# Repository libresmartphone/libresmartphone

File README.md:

Libre Smartphone - Open hardware phone
======================================

This page contains the software used in the open hardware smartphone, related projects files and documentation. Mechanical ([Freecad](http://freecadweb.org/)) and PCB schematic ([Kicad](http://kicad-pcb.org/)) designs will be added here in the future. Visit [libresmartphone.com](http://libresmartphone.com/open-hardware-smartphone/) or our [YouTube channel](https://www.youtube.com/channel/UC1UttFNKDiN2uA525Pe3ijA) for more information.

## Objective

Libresmartphone is a smartphone that can be connected to a bigger screen and used as a desktop computer to edit documents, watch videos, listen to music, edit images, videos and much more.

Our goal is to have a 6" screen, HDMI output, cameras, Bluetooth, WiFi, GPS, 4G or better and GSM. It will also have two or more micro-usb ports that will allow you to connect a printer or other peripherals.

It will be [Open Software](https://en.wikipedia.org/wiki/Open-source_software) and [Open Hardware](https://en.wikipedia.org/wiki/Open-source_hardware), designed with free software (Kicad) to let other users study, change and improve both the software and the hardware.

The design will allow one to add hardware kill switches for the camera, GPS, 4G, GSM.  This offers security & privacy for those who want full control over their devices.

## Roadmap

1. Make a [Raspberry Pi](https://www.raspberrypi.org/) prototype work as desired (Estimated time: 3 months – 1 year)(Estimated cost: <500€):
   * Software to make calls, send/receive SMS (with the [Adafruit 3G Fona](https://www.adafruit.com/product/2696) or similar), import contacts (csv) and take photos in any GNU/linux or BSD OS.
   * GPS navigation with navit.
   * Easy to make case (MDF) / CAD files to 3d print the case.
   * 7" capacitive screen from the Raspberry Pi foundation.
   * Make a manual so every user with a Raspberry Pi can achieve a working prototype easily.

   *The Raspberry Pi prototype will attract a larger user base for the project (currently there are 8 million Raspberry Pi in the market and a lot of their users are DIY enthusiast). Many of them are not willing to pay for an open source smartphone but would love to make calls with the Raspberry Pi, send SMS for their projects, build an simple GPS unit for their car, etc.*

2. Make a prototype with the components more open (Estimated time: 6 months – 4 years)(Estimated cost: 500-40.000€):
   * Use a more open HW board (A64 OLinuXino or similar) instead of the Raspberry Pi.
   * Use a more open HW screen (Manga Screen or similar) or design a 6" capacitive screen if there isn't any open hardware option available at that time (initiate a crowdfunding campaign to let others interested contribute).
   * Use a more open HW modem breakout if there is one available instead of the Adafruit 3G or design a LTE (PLS8-E) or better modem breakout (try to make a crowdfunding campaign to let others interested contribute).

   *The prototype will have replaceable parts if better / smaller alternatives appear in the market.*

   *If no suitable screens or modem breakout are found, a crowdfunding campaign will be made. The reason to make it that way is because there are other people that could want these parts for a different project and help to make it possible faster. Even if there is not enough people willing to support a crowdfunding campaign, the current people interested in making libresmartphone are able to pay Elias Bakken, Nikolaus Schaller or others to make them.*

*When the prototype has the size and requirements desired, libresmartphone development will start part 3.*

3. Libresmartphone final design (Estimated time: <2 years)(Estimated cost: 50.000-200.000€).
   * Design a pcb that has the CPU, GPU, RAM, modem, WiFi, etc in the same board taking in consideration all the designs used in part 2 of the development.
   * Design a case to fit all the components inside that is easy to 3D print. If there are enough people interested an injection case could be made.

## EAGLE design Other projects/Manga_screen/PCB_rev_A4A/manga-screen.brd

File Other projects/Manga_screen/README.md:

```                                                                                                                       
    _/      _/                                                _/_/_/                                                   
   _/_/  _/_/    _/_/_/  _/_/_/      _/_/_/    _/_/_/      _/          _/_/_/  _/  _/_/    _/_/      _/_/    _/_/_/
  _/  _/  _/  _/    _/  _/    _/  _/    _/  _/    _/        _/_/    _/        _/_/      _/_/_/_/  _/_/_/_/  _/    _/   
 _/      _/  _/    _/  _/    _/  _/    _/  _/    _/            _/  _/        _/        _/        _/        _/    _/    
_/      _/    _/_/_/  _/    _/    _/_/_/    _/_/_/      _/_/_/      _/_/_/  _/          _/_/_/    _/_/_/  _/    _/     
                                     _/                                                                                
                                _/_/                                                                                                                                                                                                          
```
Manga Screen is a 4.3" LCD panel with capacitive multi touch and HDMI input. It's been developed for use with 3D-printers, but can be used for any embedded project 
where the main board has USB and HDMI output. The license is CC BY-SA. 

### What is in here? ###

* This repository contains the files needed to reproduce the PCB and continue development.
* The latest revision is A4A

### I want to build my own board. How do I do that? ###

* Download the BOM and order the parts from Digi-key
* Send the GERBER files to a PCB manufacturer
* Get a reflow oven
* Populate the board

### Who do I talk to? ###

* Repo owner is Elias Bakken (elias dot bakken at gmail dot com) 
* Get in touch if you need Manga Screen with special requirements.

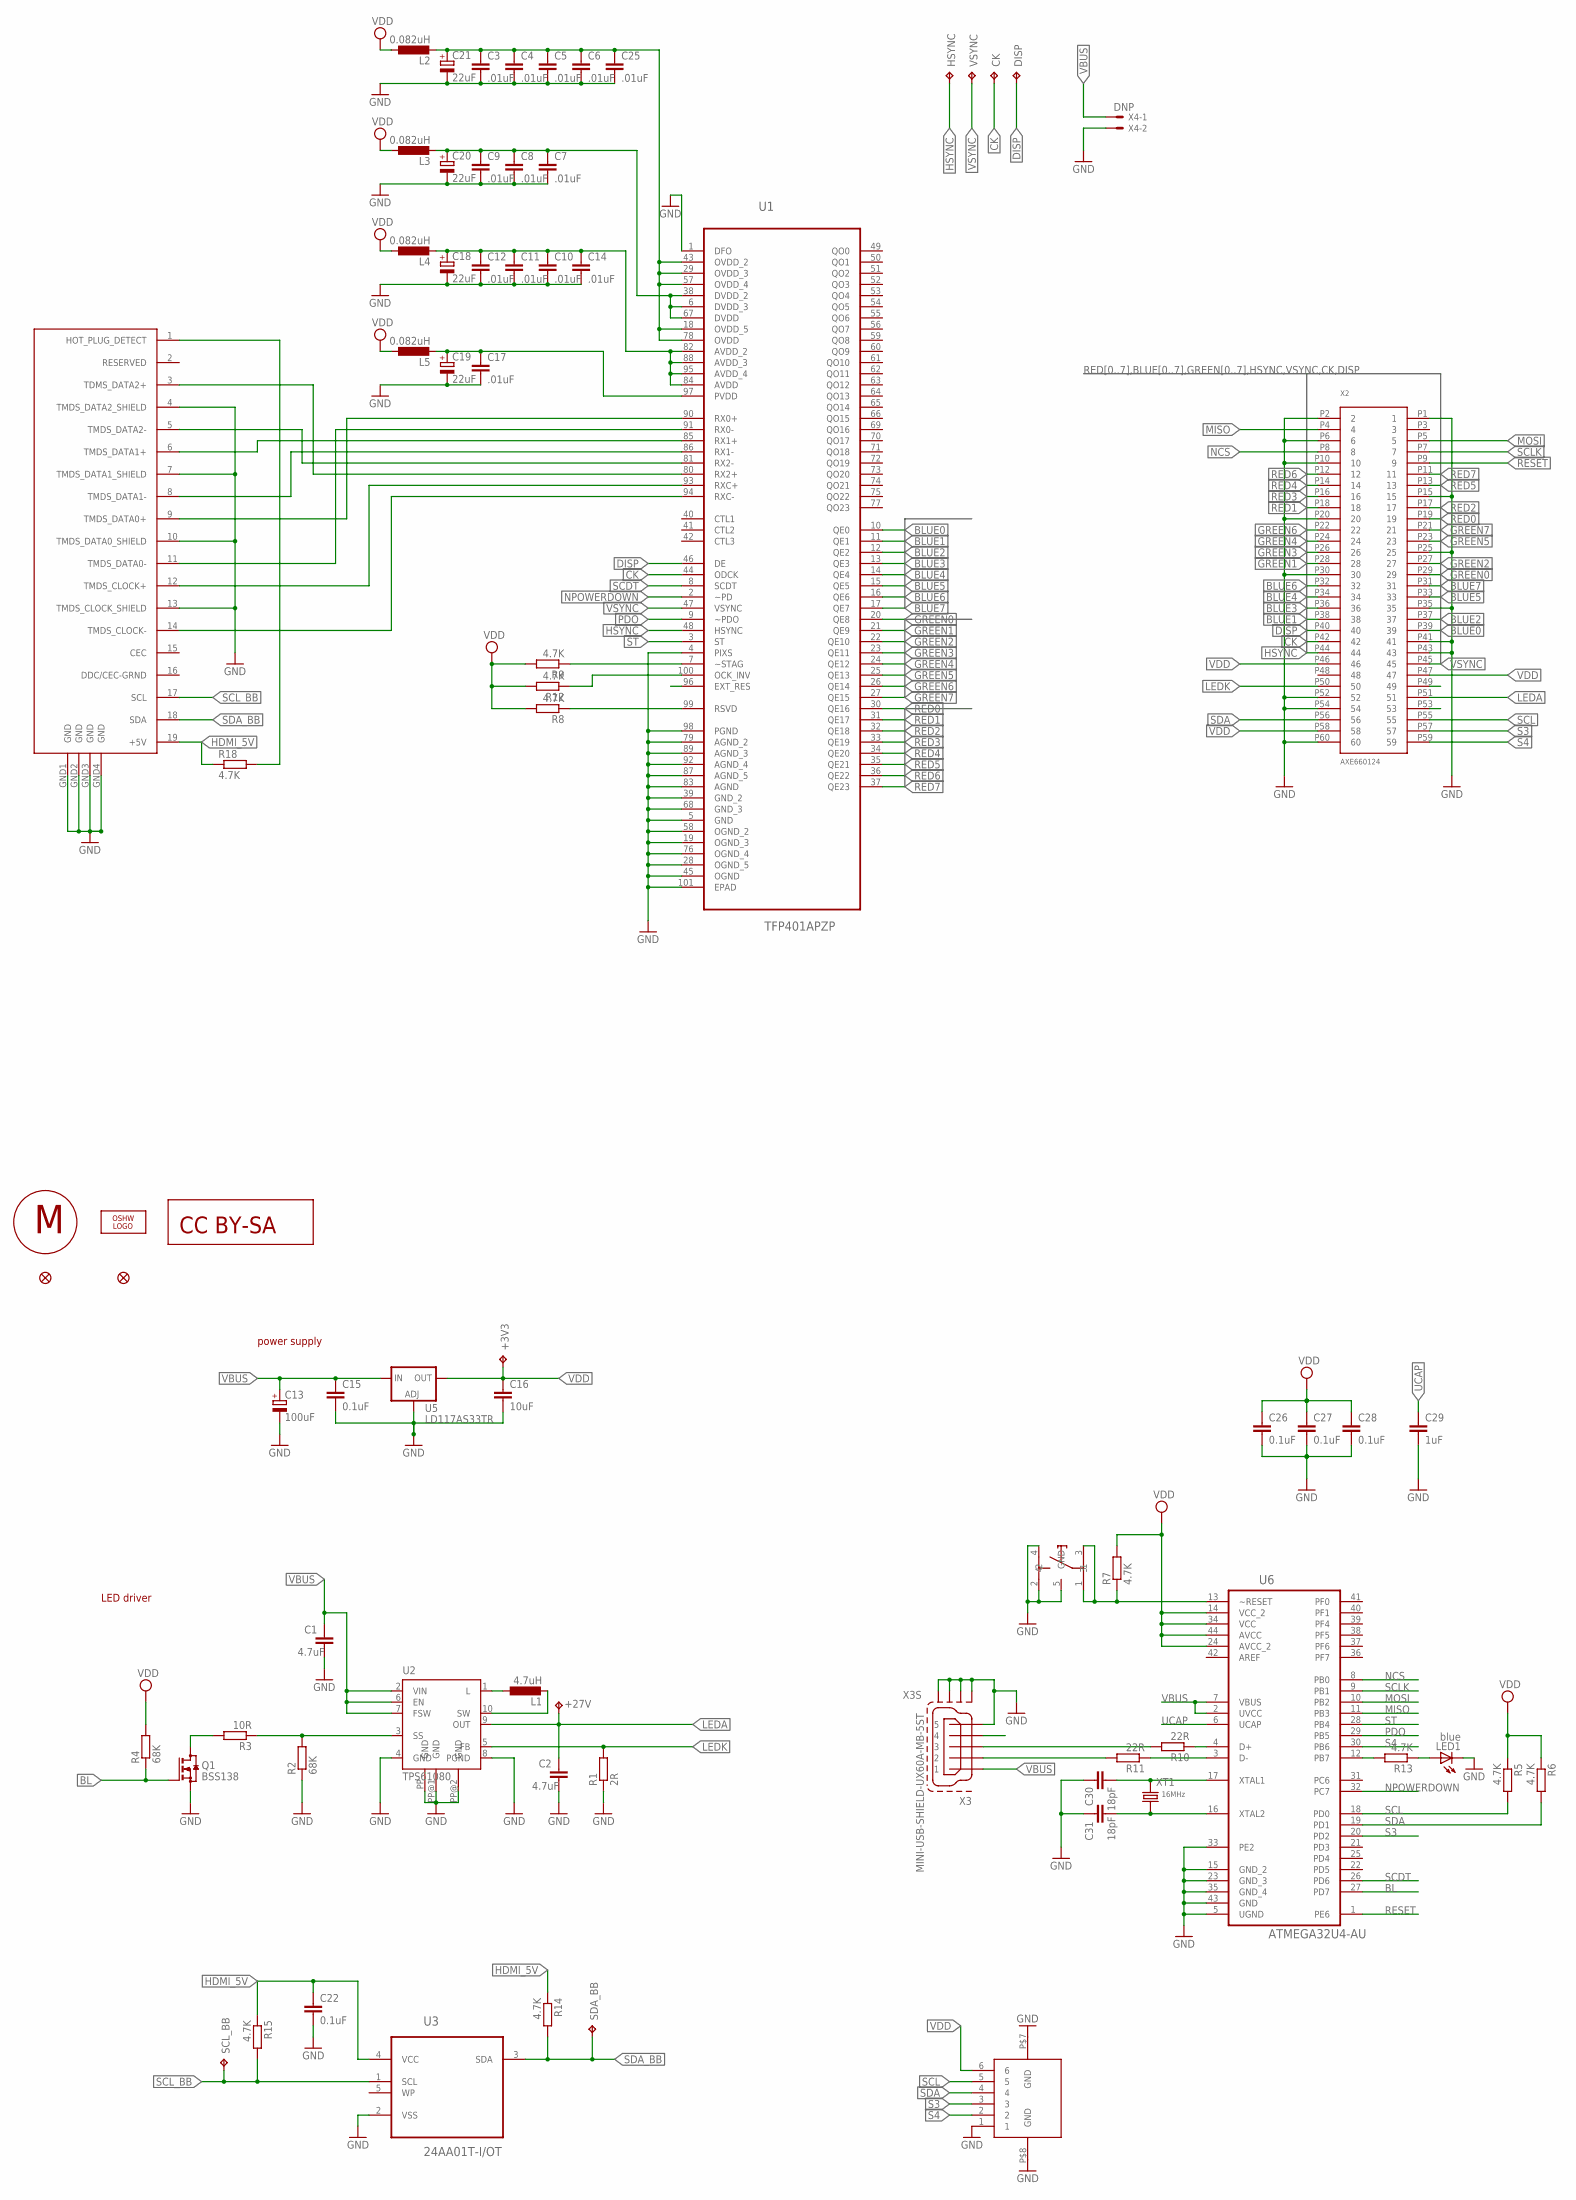
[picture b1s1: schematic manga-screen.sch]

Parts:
+3V3, +27V: TPB1,27; B1,27
C1, C2: 4.7uF; C0402
C3, C4, C5, C6, C7, C8, C9, C10, C11, C12, C14, C17, C25: .01uF; C0402
C13: 100uF; PANASONIC_B
C15, C22, C26, C27, C28: 0.1uF; C0402
C16: 10uF; C0805
C18, C19, C20, C21: 22uF; CT3216
C29: 1uF; C0402
C30, C31: 18pF; C0402
CK: TPB1,27; B1,27
DISP: TPB1,27; B1,27
HSYNC: TPB1,27; B1,27
JP1, JP2: FIDUCIAL1X2; FIDUCIAL-1X2
L1: 4.7uH; L2825P
L2, L3, L4, L5: 0.082uH; L2012C
LED1: blue; CHIP-LED0603
LOGO2: OSHW_LOGO_10MILX0200-NT; OSHW_10X200_NOTEXT
Q1: BSS138; SOT23
R1: 2R; R0402
R2, R4: 68K; R0402
R3: 10R; R0402
R5, R6, R7, R8, R9, R12, R13, R14, R15, R18: 4.7K; R0402
R10, R11: 22R; R0402
S1: KRM_TACT_SWITCH; KMR
SCL_BB: TPB1,27; B1,27
SDA_BB: TPB1,27; B1,27
U1: TFP401APZP; QFP50P1600X1600X120-101N
U2: TPS61080; S-PDSO-N10
U3: 24AA01T-I/OT; SOT95P270X145-5N
U5: LD117AS33TR; SOT223
U6: ATMEGA32U4-AU; QFP80P1200X1200X120-44N
U$1: CC-BY-SA
U$2: MANGA-GRAPHIC; MANGA
U$4: HDMI1; HDMI-D
U$5: SFV6R; SFV
VSYNC: TPB1,27; B1,27
X2: AXE660124; AXE560124
X3: MINI-USB-SHIELD-UX60A-MB-5ST; UX60A-MB-5ST
X4: DNP; 6410-02
XT1: 16MHz; 2P-SMD-5.08X3.18

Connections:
BL: Q1.1 (G), R4.1, U6.27 (PD7)
BLUE0: U1.10 (QE0), X2.P39 (39)
BLUE1: U1.11 (QE1), X2.P38 (38)
BLUE2: U1.12 (QE2), X2.P37 (37)
BLUE3: U1.13 (QE3), X2.P36 (36)
BLUE4: U1.14 (QE4), X2.P34 (34)
BLUE5: U1.15 (QE5), X2.P33 (33)
BLUE6: U1.16 (QE6), X2.P32 (32)
BLUE7: U1.17 (QE7), X2.P31 (31)
CK: CK.TP, U1.44 (ODCK), X2.P42 (42)
D+: R10.2, X3.3
D-: R11.2, X3.2
DISP: DISP.TP, U1.46 (DE), X2.P40 (40)
DM: R11.1, U6.3 (D-)
DP: R10.1, U6.4 (D+)
GND: C1.2, C2.2, C3.2, C4.2, C5.2, C6.2, C7.2, C8.2, C9.2, C10.2, C11.2, C12.2, C13.-, C14.2, C15.2, C16.2, C17.2, C18.-, C19.-, C20.-, C21.-, C22.2, C25.2, C26.2, C27.2, C28.2, C29.2, C30.1, C31.1, LED1.C, Q1.2 (S), R1.1, R2.1, S1.2, S1.4, S1.5 (GND), U1.1 (DFO), U1.4 (PIXS), U1.5 (GND), U1.19 (OGND_3), U1.28 (OGND_5), U1.39 (GND_2), U1.45 (OGND), U1.58 (OGND_2), U1.68 (GND_3), U1.76 (OGND_4), U1.79 (AGND_2), U1.83 (AGND), U1.87 (AGND_5), U1.89 (AGND_3), U1.92 (AGND_4), U1.98 (PGND), U1.101 (EPAD), U2.4 (GND), U2.8 (PGND), U2.PP (GND), U2.PP@1 (GND), U2.PP@2 (GND), U3.2 (VSS), U5.1 (ADJ), U6.5 (UGND), U6.15 (GND_2), U6.23 (GND_3), U6.33 (PE2), U6.35 (GND_4), U6.43 (GND), U$4.4 (TMDS_DATA2_SHIELD), U$4.7 (TMDS_DATA1_SHIELD), U$4.10 (TMDS_DATA0_SHIELD), U$4.13 (TMDS_CLOCK_SHIELD), U$4.GND1 (GND), U$4.GND2 (GND), U$4.GND3 (GND), U$4.GND4 (GND), U$5.1, U$5.P$7 (GND), U$5.P$8 (GND), X2.P1 (1), X2.P2 (2), X2.P6 (6), X2.P10 (10), X2.P15 (15), X2.P20 (20), X2.P25 (25), X2.P30 (30), X2.P35 (35), X2.P41 (41), X2.P43 (43), X2.P52 (52), X2.P54 (54), X2.P60 (60), X3.5, X3.M1 (S1), X3.M2 (S2), X3.M3 (S3), X3.M4 (S4), X4.2
GREEN0: U1.20 (QE8), X2.P29 (29)
GREEN1: U1.21 (QE9), X2.P28 (28)
GREEN2: U1.22 (QE10), X2.P27 (27)
GREEN3: U1.23 (QE11), X2.P26 (26)
GREEN4: U1.24 (QE12), X2.P24 (24)
GREEN5: U1.25 (QE13), X2.P23 (23)
GREEN6: U1.26 (QE14), X2.P22 (22)
GREEN7: U1.27 (QE15), X2.P21 (21)
HDMI_5V: C22.1, R14.1, R15.1, R18.1, U3.4 (VCC), U$4.19 (+5V)
HOTPLUG: R18.2, U$4.1 (HOT_PLUG_DETECT)
HSYNC: HSYNC.TP, U1.48 (HSYNC), X2.P44 (44)
LEDA: +27V.TP, C2.1, U2.9 (OUT), X2.P51 (51)
LEDK: R1.2, U2.5 (FB), X2.P50 (50)
MISO: U6.11 (PB3), X2.P4 (4)
MOSI: U6.10 (PB2), X2.P5 (5)
unnamed: L1.1, U2.1 (L)
unnamed: L1.2, U2.10 (SW)
unnamed: R12.1, U1.100 (OCK_INV)
unnamed: R2.2, R3.1, U2.3 (SS)
unnamed: Q1.3 (D), R3.2
unnamed: R7.1, S1.1, S1.3, U6.13 (~RESET)
unnamed: R13.2, U6.12 (PB7)
unnamed: LED1.A, R13.1
unnamed: R9.1, U1.7 (~STAG)
unnamed: R8.1, U1.99 (RSVD)
unnamed: C31.2, U6.16 (XTAL2), XT1.X2 (2)
unnamed: C30.2, U6.17 (XTAL1), XT1.X1 (1)
unnamed: C7.1, C8.1, C9.1, C20.+, L3.2, U1.6 (DVDD_3), U1.38 (DVDD_2), U1.67 (DVDD)
unnamed: C3.1, C4.1, C5.1, C6.1, C21.+, C25.1, L2.2, U1.18 (OVDD_5), U1.29 (OVDD_3), U1.43 (OVDD_2), U1.57 (OVDD_4), U1.78 (OVDD)
unnamed: C10.1, C11.1, C12.1, C14.1, C18.+, L4.2, U1.82 (AVDD_2), U1.84 (AVDD), U1.88 (AVDD_3), U1.95 (AVDD_4)
unnamed: C17.1, C19.+, L5.2, U1.97 (PVDD)
NCS: U6.8 (PB0), X2.P8 (8)
NPOWERDOWN: U1.2 (~PD), U6.32 (PC7)
PDO: U1.9 (~PDO), U6.29 (PB5)
RED0: U1.30 (QE16), X2.P19 (19)
RED1: U1.31 (QE17), X2.P18 (18)
RED2: U1.32 (QE18), X2.P17 (17)
RED3: U1.33 (QE19), X2.P16 (16)
RED4: U1.34 (QE20), X2.P14 (14)
RED5: U1.35 (QE21), X2.P13 (13)
RED6: U1.36 (QE22), X2.P12 (12)
RED7: U1.37 (QE23), X2.P11 (11)
RESET: U6.1 (PE6), X2.P9 (9)
S3: U6.20 (PD2), U$5.3, X2.P57 (57)
S4: U6.30 (PB6), U$5.2, X2.P59 (59)
SCDT: U1.8 (SCDT), U6.26 (PD6)
SCL: R5.2, U6.18 (PD0), U$5.5, X2.P55 (55)
SCLK: U6.9 (PB1), X2.P7 (7)
SCL_BB: R15.2, SCL_BB.TP, U3.1 (SCL), U$4.17 (SCL)
SDA: R6.2, U6.19 (PD1), U$5.4, X2.P56 (56)
SDA_BB: R14.2, SDA_BB.TP, U3.3 (SDA), U$4.18 (SDA)
ST: U1.3 (ST), U6.28 (PB4)
TMDS_CLOCK+: U1.93 (RXC+), U$4.12 (TMDS_CLOCK+)
TMDS_CLOCK-: U1.94 (RXC-), U$4.14 (TMDS_CLOCK-)
TMDS_DATA0+: U1.90 (RX0+), U$4.9 (TMDS_DATA0+)
TMDS_DATA0-: U1.91 (RX0-), U$4.11 (TMDS_DATA0-)
TMDS_DATA1+: U1.85 (RX1+), U$4.6 (TMDS_DATA1+)
TMDS_DATA1-: U1.86 (RX1-), U$4.8 (TMDS_DATA1-)
TMDS_DATA2+: U1.80 (RX2+), U$4.3 (TDMS_DATA2+)
TMDS_DATA2-: U1.81 (RX2-), U$4.5 (TMDS_DATA2-)
UCAP: C29.1, U6.6 (UCAP)
VBUS: C1.1, C13.+, C15.1, U2.2 (VIN), U2.6 (EN), U2.7 (FSW), U5.3 (IN), U6.2 (UVCC), U6.7 (VBUS), X3.1, X4.1
VDD: +3V3.TP, C16.1, C26.1, C27.1, C28.1, L2.1, L3.1, L4.1, L5.1, R4.2, R5.1, R6.1, R7.2, R8.2, R9.2, R12.2, U5.4 (OUT), U6.14 (VCC_2), U6.24 (AVCC_2), U6.34 (VCC), U6.44 (AVCC), U$5.6, X2.P46 (46), X2.P47 (47), X2.P58 (58)
VSYNC: U1.47 (VSYNC), VSYNC.TP, X2.P45 (45)

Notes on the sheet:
LED driver
power supply

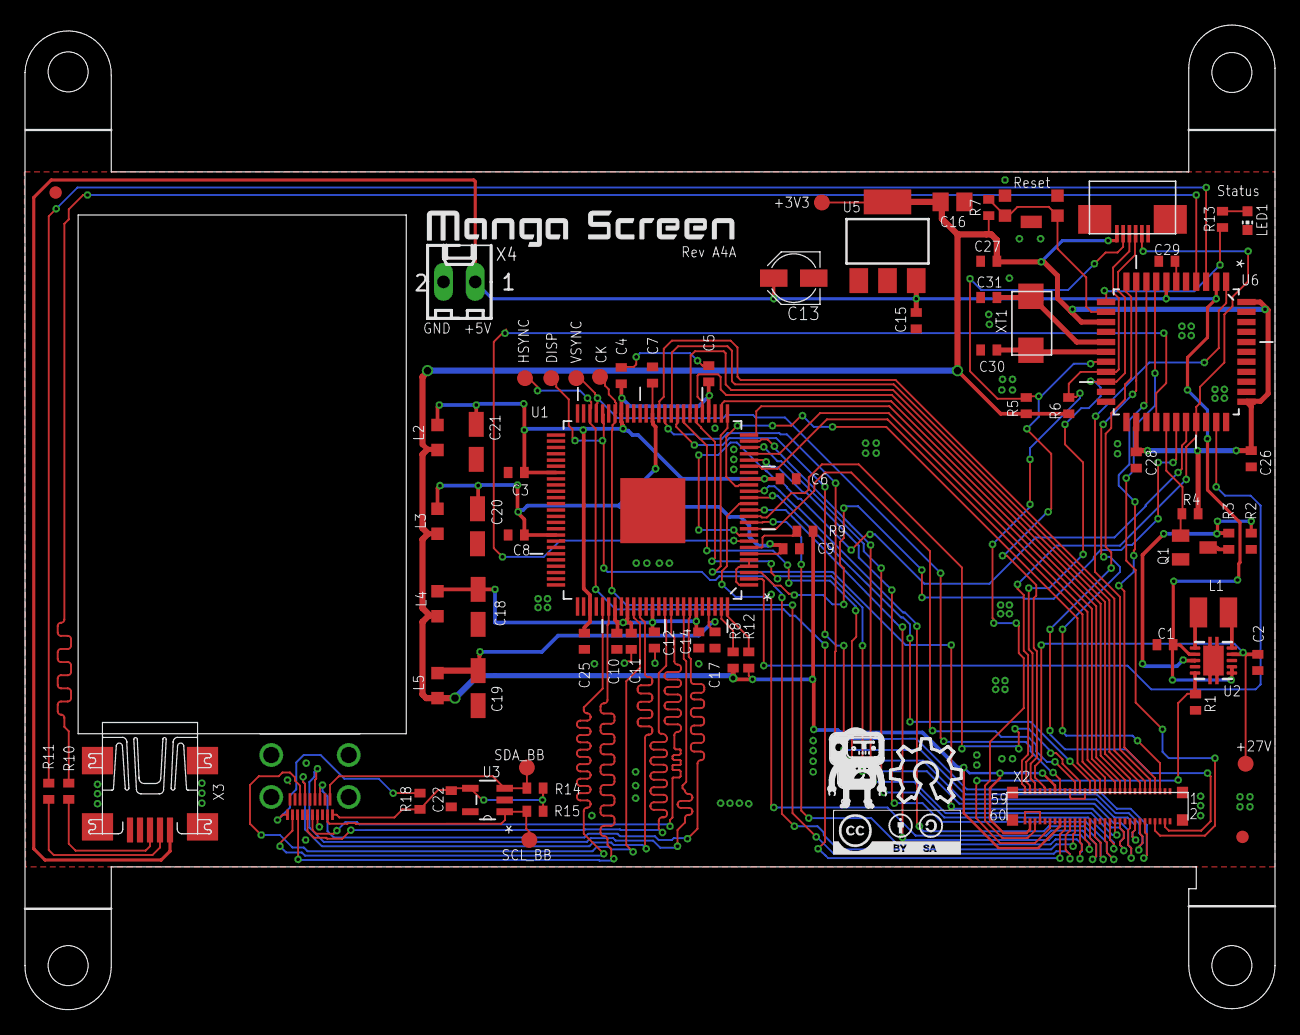
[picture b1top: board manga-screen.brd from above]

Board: 2 copper layers, 100.0 x 78.8 mm, 78 parts (1 on the bottom side), 80 nets.

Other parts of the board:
U$3: LOGO_BIG

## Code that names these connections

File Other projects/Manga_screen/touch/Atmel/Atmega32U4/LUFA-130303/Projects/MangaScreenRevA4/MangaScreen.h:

/*
             LUFA Library
     Copyright (C) Dean Camera, 2013.

  dean [at] fourwalledcubicle [dot] com
           www.lufa-lib.org
*/

/*
  Copyright 2013  Dean Camera (dean [at] fourwalledcubicle [dot] com)

  Permission to use, copy, modify, distribute, and sell this
  software and its documentation for any purpose is hereby granted
  without fee, provided that the above copyright notice appear in
  all copies and that both that the copyright notice and this
  permission notice and warranty disclaimer appear in supporting
  documentation, and that the name of the author not be used in
  advertising or publicity pertaining to distribution of the
  software without specific, written prior permission.

  The author disclaims all warranties with regard to this
  software, including all implied warranties of merchantability
  and fitness.  In no event shall the author be liable for any
  special, indirect or consequential damages or any damages
  whatsoever resulting from loss of use, data or profits, whether
  in an action of contract, negligence or other tortious action,
  arising out of or in connection with the use or performance of
  this software.
*/

/** \file
 *
 *  Header file for MangaScreen.h.
 */

#ifndef _MANGA_SCREEN_H_
#define _MANGA_SCREEN_H_

	/* Includes: */
		#include <avr/io.h>
		#include <avr/wdt.h>
		#include <avr/power.h>
		#include <avr/interrupt.h>
		#include <string.h>
        #include <stdarg.h>

		#include "Descriptors.h"
		#include "LCD.h"
		#include "Digitizer.h"
        #include "eeprom.h"

		#include <LUFA/Drivers/Board/LEDs.h>
		#include <LUFA/Drivers/Board/Buttons.h>
		#include <LUFA/Drivers/Misc/RingBuffer.h>
		#include <LUFA/Drivers/USB/USB.h>

        #include "microrl.h"
        #include "microrl/src/microrl.h"

        extern int debug_level;

	/* Macros: */
		/** LED mask for the library LED driver, to indicate that the USB interface is not ready. */
		#define LEDMASK_USB_NOTREADY      LEDS_LED2

		/** LED mask for the library LED driver, to indicate that the USB interface is enumerating. */
		#define LEDMASK_USB_ENUMERATING  (LEDS_LED1)

		/** LED mask for the library LED driver, to indicate that the USB interface is ready. */
		#define LEDMASK_USB_READY        (LEDS_LED1)

		/** LED mask for the library LED driver, to indicate that an error has occurred in the USB interface. */
		#define LEDMASK_USB_ERROR        (LEDS_LED3)

	/* Pins: */
		#define PIN_NCS   	(1<<0) // PB0
		#define PIN_SCLK  	(1<<1) // PB1
		#define PIN_MOSI  	(1<<2) // PB2
		#define PIN_MISO  	(1<<3) // PB3
		#define PIN_ST 		(1<<4) // PB4
		#define PIN_PDO		(1<<5) // PB5
		#define PIN_S4		(1<<6) // PB6

		#define PIN_PD		(1<<7) // PC7
		
		#define PIN_SCL		(1<<0) // PD0
		#define PIN_SDA		(1<<1) // PD1
		#define PIN_S3		(1<<2) // PD2
		#define PIN_SCL_BB	(1<<3) // PD3
		#define PIN_SDA_BB	(1<<5) // PD5
		#define PIN_SCDT	(1<<6) // PD6
		#define PIN_BL    	(1<<7) // PD7
		#define PIN_RESET 	(1<<6) // PE6


	/* Function Prototypes: */
		void SetupHardware(void);
		void HandleSerial(void);
		int putchar_printf(char var, FILE *stream);

        void dev_dbg(const char* format, ...);
        void dev_info(const char* format, ...);
        void dev_warn(const char* format, ...);
        void dev_err(const char* format, ...);

		void EVENT_USB_Device_Connect(void);
		void EVENT_USB_Device_Disconnect(void);
		void EVENT_USB_Device_ConfigurationChanged(void);
		void EVENT_USB_Device_ControlRequest(void);
		void EVENT_USB_Device_StartOfFrame(void);

		bool CALLBACK_HID_Device_CreateHIDReport(USB_ClassInfo_HID_Device_t* const HIDInterfaceInfo,
		                                         uint8_t* const ReportID,
		                                         const uint8_t ReportType,
		                                         void* ReportData,
		                                         uint16_t* const ReportSize);
		void CALLBACK_HID_Device_ProcessHIDReport(USB_ClassInfo_HID_Device_t* const HIDInterfaceInfo,
		                                          const uint8_t ReportID,
		                                          const uint8_t ReportType,
		                                          const void* ReportData,
		                                          const uint16_t ReportSize);
#endif

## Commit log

2015-04-20 Add Readme.txt
2015-04-20 Add kkc.py
2015-04-20 Add kk6c.py and kkh1.py
2015-04-20 Add multiplebutton2.py
2015-04-20 Add multiplebutton4.py
2015-04-21 Add multiplebutton6.py
2015-06-14 remove old files
2015-06-14 GTA02-MB-A6 contains the PCB layout in original PADS, Gerber and PDF formats.
2015-06-27 License
2015-06-28 libresmartphone software v0.1
2015-08-25 libresmartphone v0.2
    newer version of libresmartphone.
    Automatic port connection.
    Better coding
2015-08-30 Update of libresmartphone software
    Changes in this version of libresmartphone:
    · Pull calls.
    · Read SMS.
    · Level of battery.
2015-09-16 In this update (v0.3.1) The libresmartphone software can send SMS.
2015-09-20 Libresmartphone software v0.3.2. Changes: · Virtual keyboard in the sms tab.
2015-09-21 Camera software v0.1
2016-02-05 Librecalc files
2016-02-05 Own-mailbox files
2016-02-05 Neo900
2016-02-05 Manga Screen
2016-02-05 Udoo Neo http://udoo.org/download/files/schematics/
2016-02-22 Make two folders
2016-02-22 New folder
2016-02-25 Freecalypso
2016-03-14 Create New_folder
2016-03-15 SMS keyboard shows capital letters
2016-04-19 change teditdis to teditdisp in global
2016-08-07 Create OpenPandora
2016-09-24 Modify open pandora
2016-09-24 open pandora modification
2016-09-25 modify folders
2017-04-30 Move to older versions
2017-04-30 Rename Libresmartphone/Libresmartphone Software/libresmartphone_v0.3.3.py to Libresmartphone/Libresmartphone Software/Older_versions/libresmartphone_v0.3.3.py
2017-04-30 Updated without the need of connecting an arduino.
2017-04-30 Rename Libresmartphone/Libresmartphone Software/modular_private_smartphone_v0.4.0.py to Libresmartphone/Libresmartphone Software/Modular_private_smartphone_v0.4/modular_private_smartphone_v0.4.0.py
2017-04-30 Improving README
2017-05-01 Update README.md
    Add bank account and mail
2017-05-02 Update README.md
    Change and to an in line 56
2017-06-28 Zerophone addition
    Add Zerophone to other projects
2017-06-28 Update other projects with zerophone
